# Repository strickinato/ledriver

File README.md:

### LEDRIVER ###
Addressable lighting controller and accessories.

### Hardware ###
#### ledriver ####
(l-e-d river)
A teensy 3.2 versatile addressable lighting controller based on the OctoWS811 shield with lots of goodies.
- Wiznet module
- SDcard
- OLED screen
- UART breakouts
- Other clk+data output
- three buttons
- two pots
- one status led
- (piezo?? vibration detection tap tempo)

#### UI Board ####
Move pots, butons, OLED to a second poard with dedicated controller?

#### Todo ####
- Make sure teensy 3.5 fits...

#### RJPowerData ####
Connects to a ledriver board rj45 output and distributes the 4 channels of ws2811 with power.
- Fits 3.96mm and 5.08mm pitch connectors
- Fused output (microblades)
- LEDs after fuzes
- second 8p8c connector if not breaking out all the data lines.

## Firmware ##

https://forum.pjrc.com/threads/91-teensy-3-MAC-address

Sketch uses 70248 bytes (26%) of program storage space. Maximum is 262144 bytes.

### LED setup ###
Strategy : use a fixed number of LED per strips, config defines exacte number of LED per strip output. Then incomming buffers are spread to the correct slots.

#### Command System ####
- OSC based ?
- Control via serial
- network -> generate web interface?
- websocket
- osc
- map commands to dmx? brightness etc.

`/lr/brightness/ 255` -> BRIGHTNESS_CMD_BYTE + value

```
"dmx_map": {
        "0" : "/lr/brightness",
        "1" : "/lr/speed",
        "2" : "/lr/animation"
    }
```

##### Command List #####
- mode 2
- speed 255
- brightness 255
-

### webriver interface ###
Perhaps the controller should change the interface as needed. In example if set to SD card playback, populate a drop menu with names of saved animations.
- Make phone / desktop friendly.

#### LED lookup ####
- Lower Res feature? control 2 3 or 4 pixels as 1? or do in computer software...
- Add support for freeliner LED files!!

#### LED Packet ####
Reserve 2-3 bytes for controller specific info, such as :
- encode "lerp" timer and "beatCount".
- a packet type? (ramp to in X seconds);
- - command packet, append longer commands (ie save "sweetAnimation.ani");

#### Controller Commands ####
- Record animation
- play animation
- run test patterns
###### inbound
- `/record 1 (fileName)` make a filename if none provided
- `/record 0` stop recording
- `/bright 255`
- `/mode 2`
- `/speed 255`
- `/getinfo`
###### outbound

#### SD Card Saved animations
Somehow freeliner needs to to send its sync through Artnet, perhaps with sequence value?
SMPTE?
Or ArtTimeCode
Paire sequence number with lerp value?

#### Test Patterns ####
Dank test patterns for production tests.

#### config.json ####
SD card config file. Uses JSON now.
```
{

}
name=stjean
dhcp=true
ip=10.0.0.42
debug=oled
debug=Serial1/2/3
```
#### Mapping Assist ####
- Use up down button to select led,
- Set this led as the first of universe X
- Set the end?
#### Logging on SD ####
Save information as running time, errors, input frequency

#### Dependencies ####
- Ethernet
- FastLED
- SD
- SDconfigFile
- TeensyDMX

#### Optimisation ####
- between each frame pick one task from a list and increment.
    - (check websocket, check udp for OSC, ???)

### Bonus Round ###
- Its also a midi controller so you can control the software to control your controller.
- OSC controller too
- NTP time + rtc, scheduler, `schedule.scd`
- Weather
- OSC message printing on oled. Debug the network.
- pinging tool (ping list of hosts.txt)
- DMX controller,
- ArtNet controller
- DMX to usbMIDI, MIDI
- MIDI to DMX

<!-- ### Glossary ###
 - `template` set of parameters for animations, such as color and easing, templates are applied to `groups`
- `group` group of segments with a center point.
- -->
### Notes ###

##### DMX #####
- DMX+ 485A xlr pin 3 yellow
- DMX- 485B xlr pin 2 blue

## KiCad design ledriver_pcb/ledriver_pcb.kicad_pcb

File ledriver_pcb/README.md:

### Le Driver ###
AKA LED River
Multi purpose LED driver board based on Teensy and OctoWS

#### Features ####
- MicroSD card reader
- WizNET adapter footprint
- DMX output and input?
- Multiple connector choice (RJ45, )
- Serial port for connecting to other board
- Potentiometers
- Buttons
- any extra pin breakout

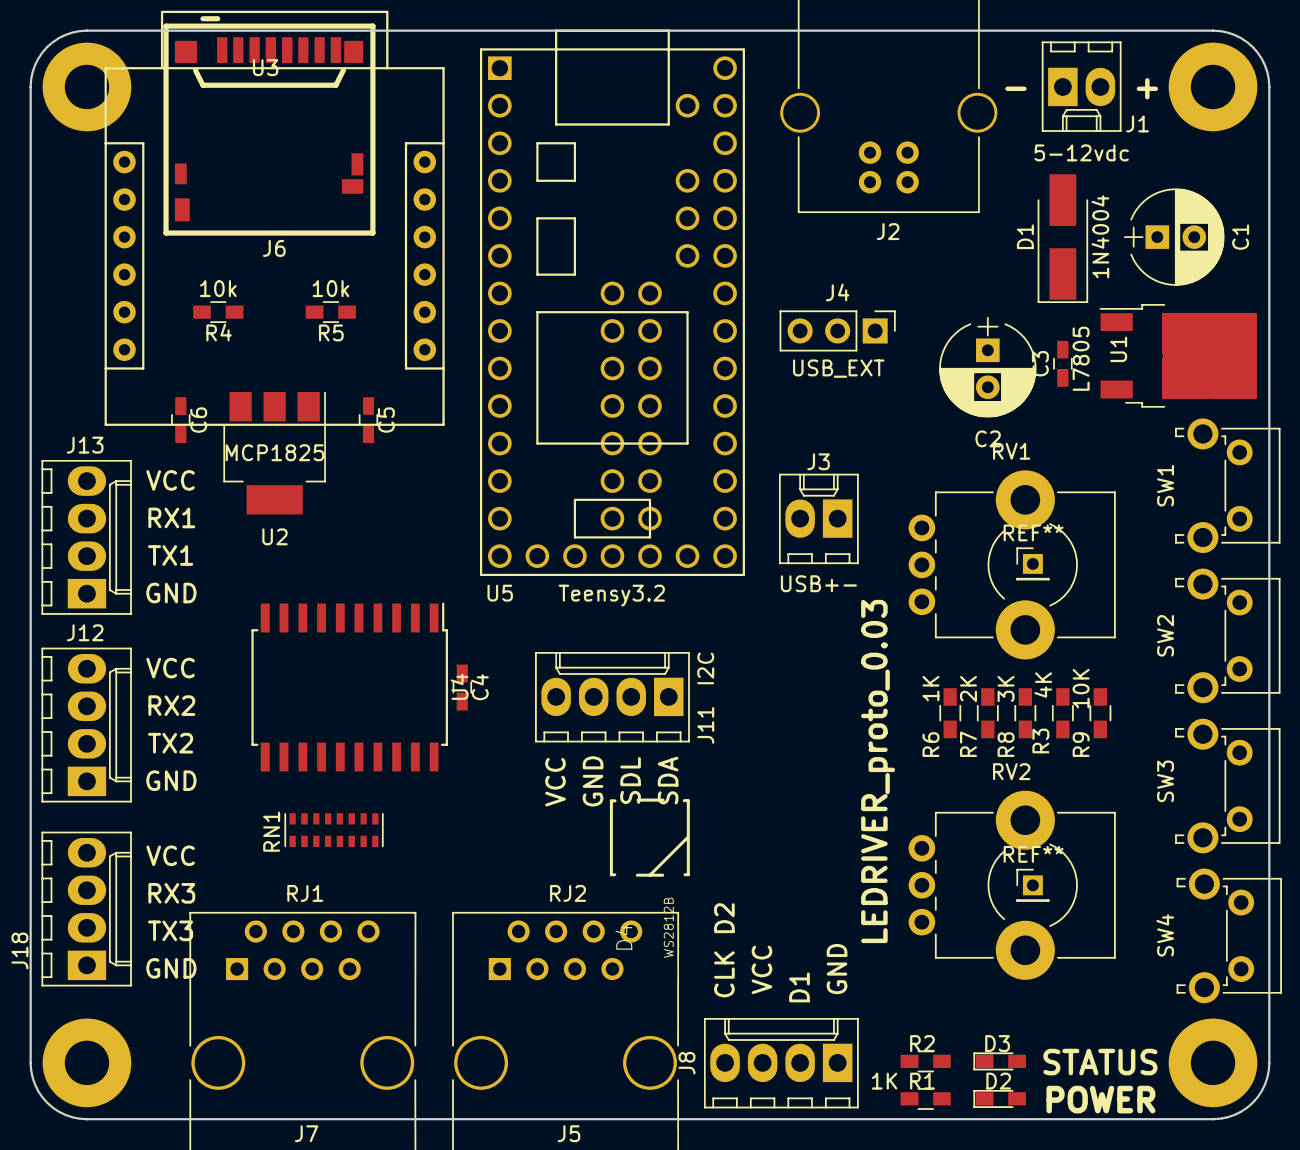
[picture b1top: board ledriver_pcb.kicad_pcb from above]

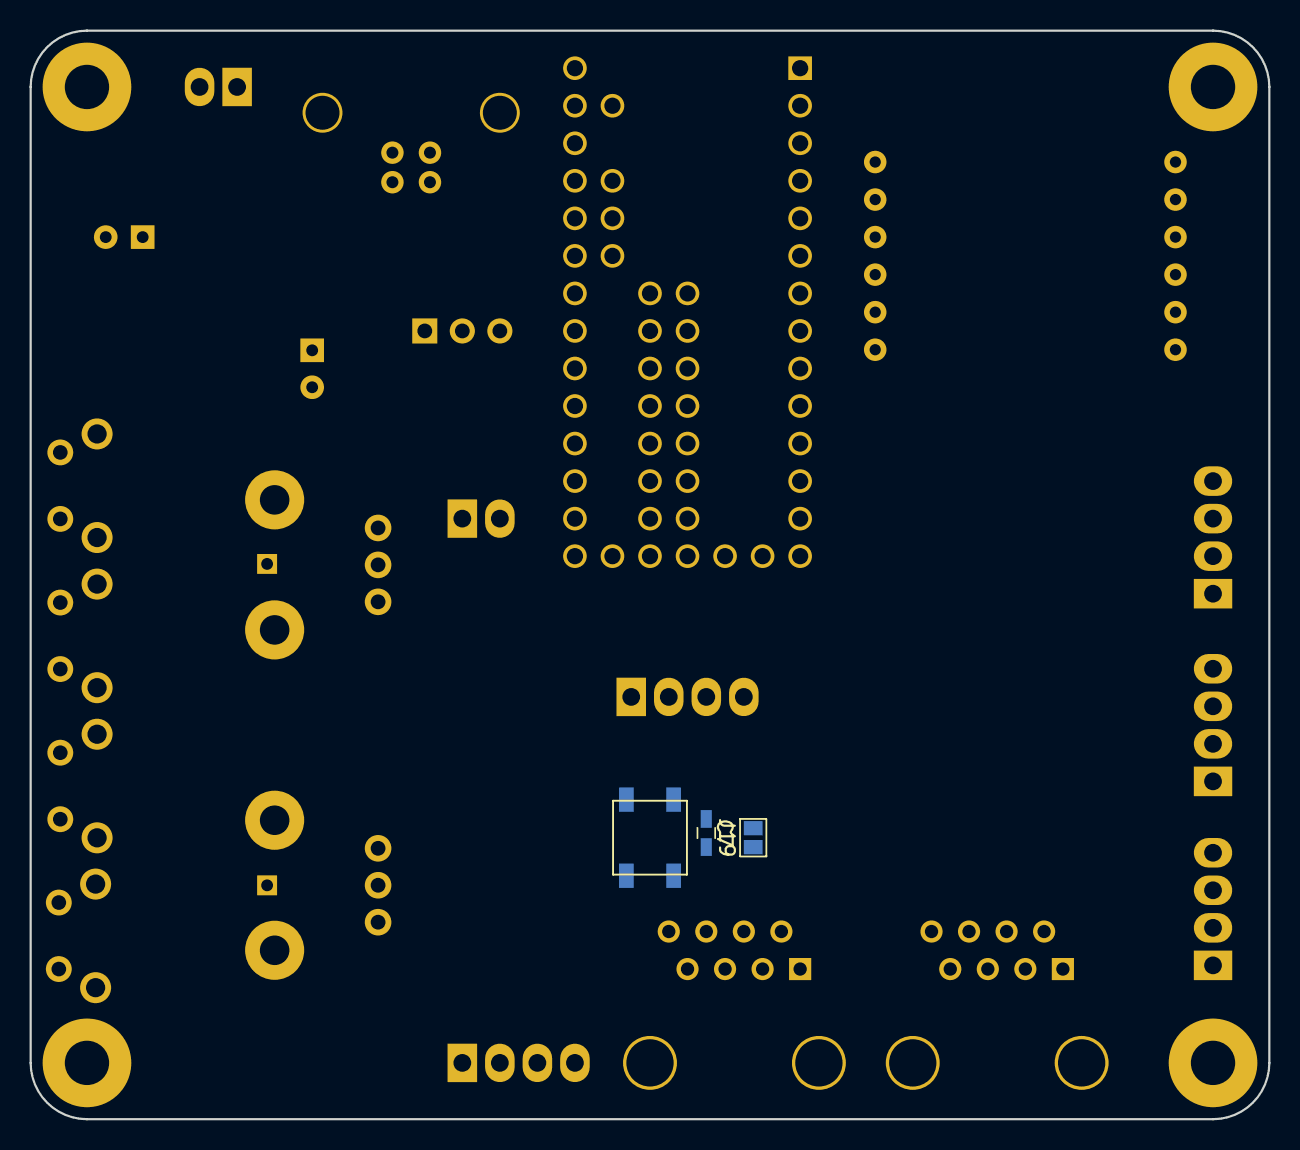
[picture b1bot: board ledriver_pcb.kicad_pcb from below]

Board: 2 copper layers, 83.8 x 73.7 mm, 49 parts (3 on the bottom side), 58 nets, no tracks yet.

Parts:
C1, C2: 47uF; CP_Radial_D6.3mm_P2.50mm
C3, C5, C6: 0.1uF; C_0603_HandSoldering
C4: 1uf; C_0603_HandSoldering
C7: C; C_0603_HandSoldering
D1: 1N4004; D_SMA_Handsoldering
D2: POWER; LED_0603_HandSoldering
D3: LED; LED_0603_HandSoldering
D4: WS2812B
J1: 5-12vdc; Molex_KK-6410-02_02x2.54mm_Straight
J2: USB_B
J3: USB+-; Molex_KK-6410-02_02x2.54mm_Straight
J4: USB_EXT; Pin_Header_Straight_1x03_Pitch2.54mm
J5: RJ2; RJ45_8_54602-908LF
J6: CONN-114-00841-68-MICROSD; AMPHENOL-114-00841-68
J7: RJ1; RJ45_8_54602-908LF
J8: led_out_clk; Molex_KK-6410-04_04x2.54mm_Straight
J11: I2C; Molex_KK-6410-04_04x2.54mm_Straight
J12: Serial2; Molex_KK-6410-04_04x2.54mm_Straight
J13: Serial1; Molex_KK-6410-04_04x2.54mm_Straight
J14, J15, J16, J17: M3; MountingHole_3mm_Pad
J18: Serial3; Molex_KK-6410-04_04x2.54mm_Straight
J19: underglow; GS2
R1, R2, R6: 1K; R_0603_HandSoldering
R3: 4K; R_0603_HandSoldering
R4, R5: 10k; R_0603_HandSoldering
R7: 2K; R_0603_HandSoldering
R8: 3K; R_0603_HandSoldering
R9: 10K; R_0603_HandSoldering
RN1: R_100; R_Cat16-8
RV1, RV2: POT; Potentiometer_Bourns_PTV09A-1_Horizontal
SW1, SW2, SW3, SW4: SW_SPST; SW_Tactile_SPST_Angled_PTS645Vx39-2LFS
U1: L7805; TO-252-2
U2: MCP1825; SOT-223-3_TabPin2
U3: WIZ820IO
U4: 74HC245; SOIC-20W_7.5x12.8mm_Pitch1.27mm
U5: Teensy3.2; Teensy30_31_32_LC

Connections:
+3V3: R3.1, R6.1, R7.1, R8.1, RV1.1, RV2.1, U5.31
+12V: D1.2, J1.2
/BUTTONS: R9.2, SW1.1, SW2.1, SW3.1, SW4.1, U5.24
/DATA_1_PIN_2: U4.2, U5.4
/DATA_2_PIN_14: U4.3, U5.21
/DATA_3_PIN_7: J18.3, U4.4, U5.9
/DATA_4_PIN_8: J18.2, U4.5, U5.10
/DATA_5_PIN_6: U4.6, U5.8
/DATA_6_PIN_20: U4.7, U5.27
/DATA_7_PIN_21: U4.8, U5.28
/DATA_8_PIN_5: U4.9, U5.7
/I2C_SCL: J11.2, U5.26
/I2C_SDA: J11.1, U5.25
/POT1: RV1.2, U5.22
/POT2: RV2.2, U5.23
/RX1: J13.3, U5.2
/RX2: J12.3, U5.11
/SPI_CS_SDCARD: J6.2, R5.2, U5.5
/SPI_CS_WIZ: R4.2, U3.5, U5.6
/SPI_DIN: J6.7, U3.7, U5.14
/SPI_DOUT: J6.3, U3.3, U5.13
/SPI_SCK: J6.5, U3.4, U5.20
/STATUS: D3.2, U5.29
/TX1: J13.2, U5.3
/TX2: J12.2, U5.12
/WIZ_RESET: U3.8, U5.30
GND: C1.2, C2.2, C3.2, C4.2, C5.2, C6.2, C7.2, D4.3, J1.1, J2.4, J2.5, J5.1, J5.3, J5.5, J5.7, J6.6, J6.11, J7.1, J7.3, J7.5, J7.7, J8.1, J11.3, J12.1, J13.1, J18.1, R1.2, R2.1, U1.2, U2.2, U3.1, U3.2, U3.12, U4.10, U4.19, U5.1
GNDA: R9.1, RV1.3, RV2.3, U5.32
unnamed: C1.1, D1.1, U1.1
unnamed: C2.1, C3.1, J4.1, U1.3
unnamed: C6.1, J6.4, R4.1, R5.1, U2.3, U3.10, U3.11
unnamed: D2.1, R1.1
unnamed: D3.1, R2.2
unnamed: D4.4, J19.1
unnamed: J2.1, J4.3
unnamed: J2.2, J3.1
unnamed: J2.3, J3.2
unnamed: J5.2, RN1.12
unnamed: J5.4, RN1.11
unnamed: J5.6, RN1.10
unnamed: J5.8, RN1.9
unnamed: J7.4, J8.4, RN1.15
unnamed: J7.6, RN1.14
unnamed: J7.8, RN1.13
unnamed: J7.2, J8.2, J19.2, RN1.16
unnamed: R3.2, SW4.2
unnamed: R6.2, SW1.2
unnamed: R7.2, SW2.2
unnamed: R8.2, SW3.2
unnamed: RN1.1, U4.18
unnamed: RN1.2, U4.17
unnamed: RN1.3, U4.16
unnamed: RN1.4, U4.15
unnamed: RN1.5, U4.14
unnamed: RN1.6, U4.13
unnamed: RN1.7, U4.12
unnamed: RN1.8, U4.11
VCC: C4.1, C5.1, C7.1, D2.2, D4.1, J4.2, J8.3, J11.4, J12.4, J13.4, J18.4, U2.1, U4.1, U4.20, U5.33

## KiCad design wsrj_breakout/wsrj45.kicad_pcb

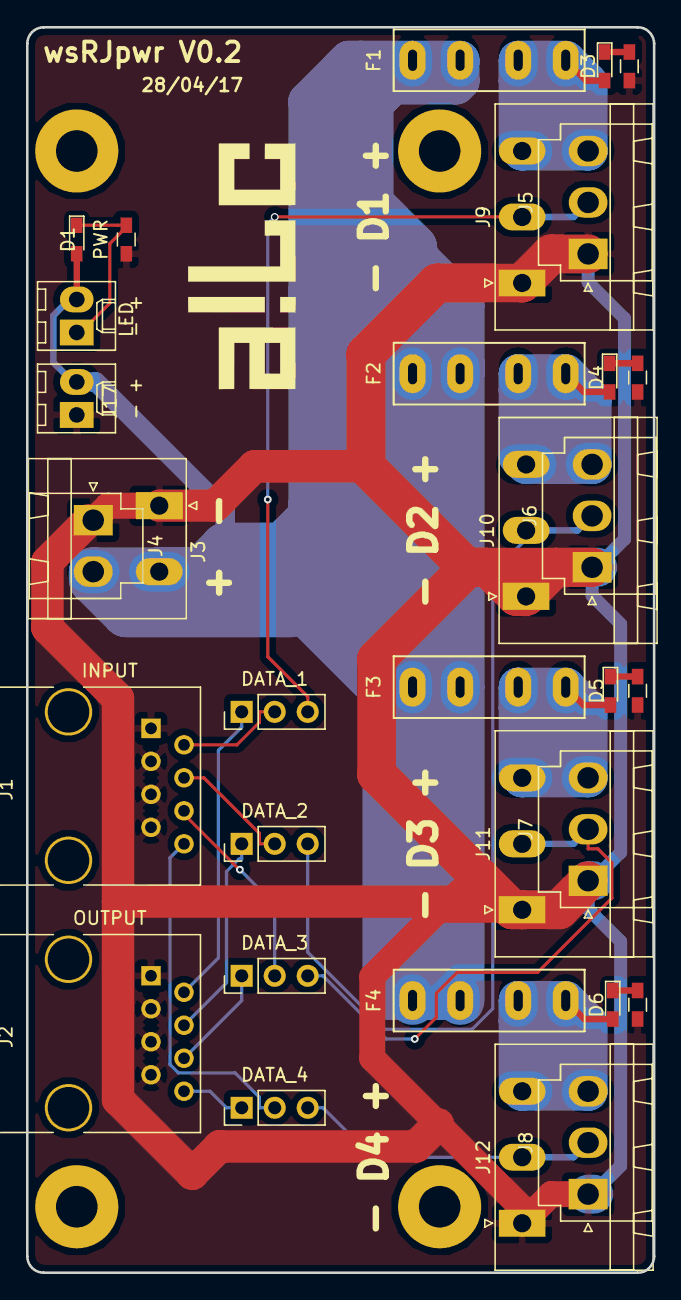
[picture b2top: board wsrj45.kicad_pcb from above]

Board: 2 copper layers, 48.3 x 95.9 mm, 36 parts (0 on the bottom side), 23 nets.

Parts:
D1: PWR; LED_0603_HandSoldering
D3: PWR_1; LED_0603_HandSoldering
D4: PWR_2; LED_0603_HandSoldering
D5: PWR_3; LED_0603_HandSoldering
D6: PWR_4; LED_0603_HandSoldering
F1, F2, F3, F4: Fuse; MINI_FUSE_HOLDER
J1: INPUT; RJ45_8_54602-908LF
J2: OUTPUT; RJ45_8_54602-908LF
J3: DC_IN; PhoenixContact_MSTBA-G_02x5.08mm_Angled
J4: DC_IN; JST_VH_B2P-VH-B_2x3.96mm_Vertical
J5: DATA_1; JST_VH_B3P-VH_3x3.96mm_Vertical
J6: DATA_2; JST_VH_B3P-VH_3x3.96mm_Vertical
J7: DATA_3; JST_VH_B3P-VH_3x3.96mm_Vertical
J8: DATA_4; JST_VH_B3P-VH_3x3.96mm_Vertical
J9, J10, J11, J12: Conn_01x03; PhoenixContact_MSTBA-G_03x5.08mm_Angled
J13, J14, J15, J16: Conn_01x01; MountingHole_3.2mm_M3_Pad
J17: - +; Molex_KK-6410-02_02x2.54mm_Straight
J18: DATA_4; Socket_Strip_Straight_1x03_Pitch2.54mm
J19: DATA_3; Socket_Strip_Straight_1x03_Pitch2.54mm
J20: DATA_2; Socket_Strip_Straight_1x03_Pitch2.54mm
J21: DATA_1; Socket_Strip_Straight_1x03_Pitch2.54mm
LED: - +; Molex_KK-6410-02_02x2.54mm_Straight
R1, R2, R3, R4, R5: R; R_0603_HandSoldering

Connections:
/DATA_1: J5.2, J9.2, J21.3
/DATA_2: J6.2, J10.2, J20.3
/DATA_3: J7.2, J11.2, J19.3
/DATA_4: J8.2, J12.2, J18.3
/VCC_1: D3.2, F1.1, J5.3, J9.3
/VCC_2: D4.2, F2.1, J6.3, J10.3
/VCC_3: D5.2, F3.1, J7.3, J11.3
/VCC_4: D6.2, F4.1, J8.3, J12.3
GND: J1.1, J1.3, J1.5, J1.7, J2.1, J2.3, J2.5, J2.7, J3.1, J4.1, J5.1, J6.1, J7.1, J8.1, J9.1, J10.1, J11.1, J12.1, J17.1, R1.2, R2.2, R3.2, R4.2, R5.2
unnamed: D1.1, LED.1, R1.1
unnamed: D3.1, R2.1
unnamed: D4.1, R3.1
unnamed: D5.1, R4.1
unnamed: D6.1, R5.1
unnamed: J1.2, J21.2
unnamed: J1.4, J20.2
unnamed: J1.6, J19.2
unnamed: J1.8, J18.2
unnamed: J2.2, J21.1
unnamed: J2.4, J20.1
unnamed: J2.8, J18.1
unnamed: J2.6, J19.1
VCC: D1.2, F1.2, F2.2, F3.2, F4.2, J3.2, J4.2, J17.2, LED.2

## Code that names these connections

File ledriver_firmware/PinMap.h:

#ifndef PinMap_h
#define PinMap_h

// All the pins
#define RX1_PIN 0
#define TX1_PIN 1
#define DATA_1_PIN  2
// #define SDCARD_CS_PIN 3
// #define WIZNET_CS_PIN 4
#define SDCARD_CS_PIN 3
#define WIZNET_CS_PIN 10
#define DATA_8_PIN  5
#define DATA_5_PIN  6
#define DATA_3_PIN  7
#define DATA_4_PIN  8
#define RX2_PIN 9
#define TX2_PIN 10
#define SPI_DOUT_PIN 11
#define SPI_DIN_PIN 12

#define SPI_CLK_PIN 13
#define DATA_2_PIN 14
#define POT1_PIN 15
#define POT2_PIN 16
#define BUTTON_PIN 17
#define I2C_SDA_PIN 18
#define I2C_SCL_PIN 19
#define DATA_6_PIN 20
#define DATA_7_PIN 21
#define STATUS_LED_PIN 22
#define WIZNET_RESET_PIN 23

#endif

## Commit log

2018-01-11 first prototype ledRiver
2018-01-12 new ledriver layout
2018-01-26 first code commit of the burrito supreme
2018-01-26 board detween v02 and v03
2018-01-26 readme
2018-01-26 more info
2018-02-15 implemted mode system
2018-02-19 moving right along
2018-02-22 basic artnet works
2018-03-12 with dmx
2018-03-21 parse mac address from sdcard
2018-04-05 added Ethernet.init(pin)
2018-04-28 pre wsrj45 data ligne fix
2018-04-28 v02 of power distribution
2018-05-18 pre switching to arduino-json
2018-05-18 unsing teensyMAC and renamed View
2018-05-20 pre websocket test
2018-05-20 basic socket connection
2018-05-21 pre removal of mode
2018-05-25 slowly comming together
2018-05-27 pre buffer spike
2018-05-27 does not seem to work
2018-05-27 compiles, but crashes on startup
2018-05-27 very abstracted works
2018-05-27 merging back
2018-05-28 changed led SPI output to use pin 7 and 14, not reflected in layout
2018-06-07 websocket osc, not sure if its the right solution
2018-06-07 haha
2018-06-07 hjaha
2018-06-10 thejson route
2018-06-10 json defined web interface no callbacks yet
2018-06-10 swapping a few pins to fix ehternet SPI CS thing
2018-06-10 controls a color from webpage!
2018-06-12 webgui can push new configs
2018-06-13 pre refactor webgui
2018-06-13 pre factor webgui
2018-06-13 weird bug with select objects dissapearing
2018-06-13 divided setup into config, led, and dmx
2018-06-14 dmx output tested
2018-06-15 dmx outputs setable to universes
2018-06-21 pre debug universe stuffing
2018-06-21 works at spore
2018-11-01 added ws2801 leds, not quite working....
2018-11-01 fixed zero indexing bug with artnet, ws2801 works with artnet
2018-11-02 post fall1 end of batch party
2018-11-05 Parse the websocket data to drive LEDs
2018-11-05 work to create a separate Mode for receiving LED data via websocket
2018-11-05 bunchof debugging because PARSING of incoming JSON is NOT WORKING!
